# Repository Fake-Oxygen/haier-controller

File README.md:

# Haier Heat Pump Controller

Custom controller and monitoring interface for Haier heat pumps using the **YR-E27 remote-control interface / Modbus RTU**.

The project combines an embedded controller, custom hardware, firmware, and host-side tools for communicating with and monitoring the heat pump.

## Overview

The controller interfaces directly with the heat pump's communication bus and provides access to operational data and control parameters that are otherwise handled by the original control system.

The system is built around an **ESP32-C6** running **Zephyr RTOS**. The controller communicates with the heat pump over UART/Modbus RTU and exposes selected telemetry and control functionality through Wi-Fi and MQTT.

The repository also contains hardware and mechanical design files, as well as software utilities used for protocol investigation, testing, and monitoring.

## System Architecture

```text
                    ┌─────────────────────┐
                    │    Haier Heat Pump  │
                    │                     │
                    │  YR-E27 / Modbus RTU│
                    └──────────┬──────────┘
                               │
                         UART / RS-485
                               │
                    ┌──────────▼──────────┐
                    │   ESP32-C6          │
                    │                     │
                    │   Zephyr RTOS       │
                    │   Modbus client     │
                    │   Heat pump driver  │
                    │   Control logic     │
                    └───────┬───────┬─────┘
                            │       │
                          Wi-Fi    GPIO
                            │       │
                     ┌──────▼───┐   ├── Relay outputs
                     │   MQTT   │   └── Status / sensors
                     └──────────┘
```

The exact hardware interfaces and signal routing are documented in the hardware design files.

## Heat Pump Communication

The main purpose of the project is direct communication with the Haier heat pump.

Communication uses **Modbus RTU over UART**. The firmware implements the required register access and translates the heat pump's register data into higher-level operating parameters.

The implementation currently provides access to parameters including:

* CH temperature
* DHW temperature
* CH target temperature
* DHW target temperature
* Operating mode
* Valve state
* Tank status
* Heater operating state
* Other system status registers

The firmware can also write supported registers to change selected operating parameters.

The register definitions and protocol implementation are located in the firmware sources.

## Hardware

The controller is based on an **ESP32-C6**.

The hardware provides interfaces for:

* Heat pump communication
* Wi-Fi
* Temperature measurement
* Relay/control outputs
* Status indication

The complete hardware design is located in [`hw/`](./hw).

Refer to the schematics and PCB files there for the actual electrical implementation.

## Mechanical Design

Mechanical parts and enclosure designs are located in [`hwm/`](./hwm).

The enclosure is designed around the controller hardware and its intended installation environment.

Available CAD/manufacturing files should be treated as the authoritative source for dimensions and mechanical details.

## Firmware

The embedded firmware is located in [`fw/`](./fw).

It is written in **C** and uses **Zephyr RTOS**.

The firmware is responsible for:

* Modbus communication with the heat pump
* Register decoding
* Heat pump state/control handling
* Wi-Fi connectivity
* MQTT communication
* Telemetry publishing
* Local I/O such as relays and sensors

The main application and hardware-specific code are organized within the firmware tree.

## MQTT

The controller publishes heat pump telemetry over MQTT, allowing the data to be consumed by external systems such as home-automation or monitoring software.

Telemetry is encoded using **CBOR** before being published.

The MQTT interface is implemented in the firmware and is intended to decouple the heat pump interface from higher-level monitoring and automation systems.

## Host-Side Tools

The [`sw/`](./sw) directory contains software used during development and operation of the system.

These tools are separate from the ESP32 firmware and are useful for tasks such as:

* Monitoring communication
* Testing the heat pump interface
* Experimenting with the protocol
* Simulating heat pump behavior

In particular, `sniffer.py` and `mock_heatpump.py` are used for working with the communication protocol without necessarily relying on the complete embedded system.

## Building the Firmware

The firmware uses the Zephyr build system and `west`.

Initialize the project:

```bash
./init.sh
```

Build for the target board:

```bash
west build -p auto -b esp32c6_devkitc_hpcore
```

Flash the resulting firmware:

```bash
west flash
```

The required Zephyr SDK and Python dependencies must be installed before building.

## Repository Structure

```text
.
├── fw/                  # ESP32-C6 firmware
│   ├── src/             # Application code
│   ├── drivers/         # Hardware / heat pump drivers
│   └── boards/          # Board-specific configuration
│
├── hw/                  # Electronics design
│   ├── ...              # Schematics / PCB files
│   └── ...
│
├── hwm/                 # Mechanical design
│   ├── ...              # CAD / STL files
│   └── ...
│
├── sw/                  # Host-side tools
│   ├── sniffer.py       # Protocol analysis tool
│   ├── mock_heatpump.py # Heat pump simulator
│   └── ...
│
└── README.md
```

## Development Status

This repository contains an actively developed controller and reverse-engineering effort for interfacing with the Haier heat pump communication system.

The firmware, hardware, and host-side tooling are maintained together because development of the controller depends on understanding and testing the heat pump's communication protocol.

For the current implementation status, refer to the firmware and software sources rather than assuming that every documented interface is production-ready.

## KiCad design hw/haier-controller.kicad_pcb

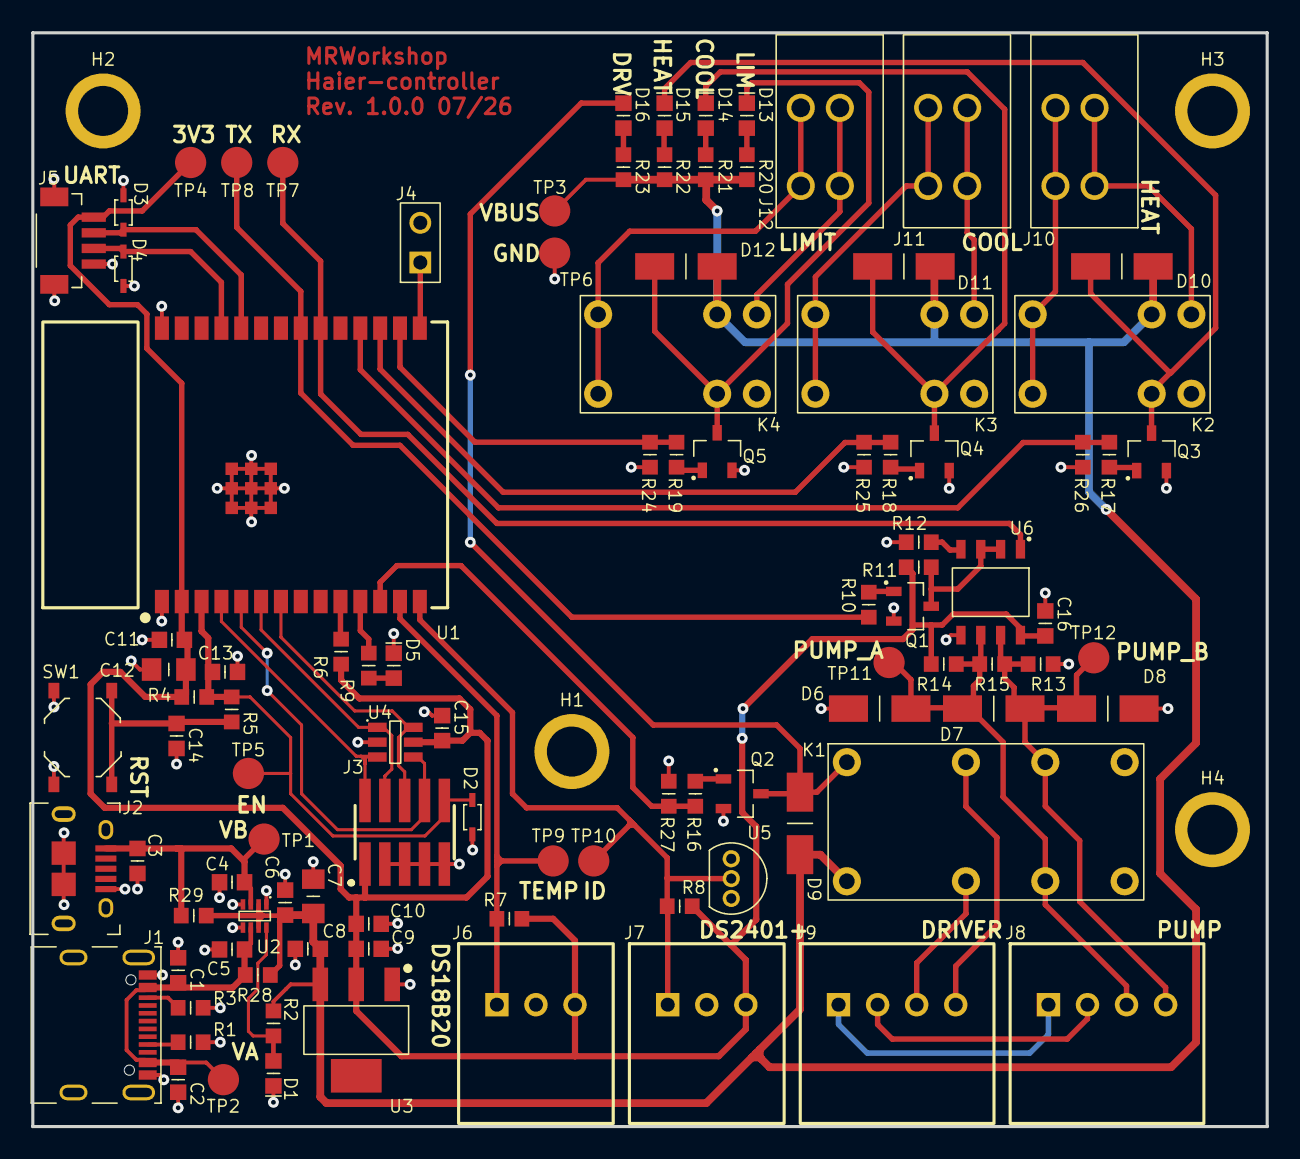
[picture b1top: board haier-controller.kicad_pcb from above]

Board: 2 copper layers, 79.0 x 70.0 mm, 105 parts (0 on the bottom side), 55 nets.

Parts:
C1, C2, C3, C13: 1u; C_0603
C4, C5, C6, C8, C9, C11, C14, C15, C16: 100n; C_0603
C7: 10u; C_0805
C10: 10u; C_0603
C12: 22uF; C_0805
D1, D5, D13, D14, D15, D16: Green; LED_0603
D2, D3, D4: STS321033B100; SOD-323
D6, D7, D8: SMAJ12CA-13-F; SMA
D9, D10, D11, D12: M7; SMA
H1, H2, H3, H4: M3; M3-Hole
J1: USB4105-GF-A
J2: 10118194-0001LF
J3: FTSH-105-01-L-DV-K
J4: Goldpin; Goldpin 2.54mm 1x2 Vertical
J5: BM04B; BM04B-SRSS-TB (LF)(SN)
J6, J7: S3B-XH-A-1; S3B-XH-A-1 (LF)(SN)
J8, J9: S4B-XH-A-1; S4B-XH-A-1 (LF)(SN)
J10, J11, J12: DG240W; DG240W-2.54-02P-15-00A(H)
K1: HFD27-005-S
K2, K3, K4: HFD23/005-1ZS; HFD23-005-1ZS
Q1, Q2, Q3, Q4, Q5: MMBT3904; SOT-23
R1, R3: 5k1; R_0603
R2, R9, R16, R17, R18, R19, R20, R21, R22, R23: 1k; R_0603
R4, R6, R24, R25, R26, R27: 10k; R_0603
R5, R12, R28, R29: 0R; R_0603
R7, R8, R10, R11, R13, R14: 4k7; R_0603
R15: 120R; R_0603
SW1: PTS526SM15SMTR2_LFS
TP1, TP2, TP3, TP4, TP5, TP6, TP7, TP8, TP9, TP10, TP11, TP12: TestPoint-2mm
U1: ESP32-C6; ESP32-C6-WROOM-1
U2: LM66200DRLR; SOT8
U3: LD1117S33CTR; SOT-223
U4: USBLC6-4SC6; SOT23-6L
U5: DS2401+; TO-92
U6: MAX3485EESA+T; SO8

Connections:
+3.3V: C9.2, C10.2, C11.2, C12.2, C15.2, C16.1, J3.1 (VREF), J5.1, J6.3, J7.3, R4.1, R6.2, R7.1, R8.1, R11.1, R14.1, TP4.1, U1.2 (3V3), U3.2 (VOUT), U4.5 (VBUS), U6.8 (VCC)
/1W_ID: J7.1, R8.2, TP10.1, U1.14 (IO13), U5.2 (DATA)
/COOL_SW: R18.2, R25.2, U1.17 (IO19)
/DRV_A: J9.3, K1.7 (NC2)
/DRV_B: J9.4, K1.2 (NC1)
/DS18B20: J6.1, R7.2, TP9.1, U1.13 (IO12)
/ESP_EN: C13.2, D2.2, J3.10 (RST), R4.2, R5.1, TP5.1, U1.3 (EN)
/ESP_TCK: J3.4 (TCK/SWDCLK), U1.6 (IO6), U4.1 (I/O1)
/ESP_TDI: J3.8 (TDI), U1.5 (IO5), U4.4 (I/O3)
/ESP_TDO: J3.6 (TDO/SWO), U1.7 (IO7), U4.6 (I/O4)
/ESP_TMS: J3.2 (TMS/SWDIO), U1.4 (IO4), U4.3 (I/O2)
/HEAT_SW: R17.2, R26.2, U1.18 (IO20)
/LIM_SW: R19.2, R24.2, U1.16 (IO18)
/PUMP_A: D6.1, D7.2, J8.3, K1.6 (COM2), R14.2, R15.1, TP11.1, U6.6 (A)
/PUMP_B: D7.1, D8.2, J8.4, K1.3 (COM1), R13.1, R15.2, TP12.1, U6.7 (B)
/PUMP_RX: TP7.1, U1.20 (IO22), U6.1 (RO)
/PUMP_TX: R10.1, TP8.1, U1.21 (IO23)
/RS_SWITCH: R16.2, R27.2, U1.12 (IO11)
GND: C1.1, C2.1, C3.1, C4.1, C5.1, C6.1, C7.1, C8.1, C9.1, C10.1, C11.1, C12.1, C13.1, C14.1, C15.1, C16.2, D1.1, D2.1, D3.1, D4.1, D5.1, D6.2, D8.1, H1.1, H2.1, H3.1, H4.1, J1.A1 (GND), J1.A12 (GND), J1.SH (Shield), J2.5 (GND), J2.SH, J3.3 (GND), J3.5 (GND), J3.7 (VDD), J3.9 (GND), J4.2, J5.4, J5.SH, J6.2, J7.2, Q1.3 (E), Q2.3 (E), Q3.3 (E), Q4.3 (E), Q5.3 (E), R1.1, R3.1, R12.2, R13.2, R24.1, R25.1, R26.1, R27.1, SW1.2, TP6.1, U1.1 (GND), U1.28 (GND), U1.29 (EPAD), U2.1 (GND), U2.4 (~ON), U2.5 (GND), U3.1 (GND), U4.2 (GND), U5.1 (GND), U6.5 (GND)
unnamed: C14.2, R5.2, SW1.1
unnamed: D5.2, R9.1
unnamed: D13.2, R20.2
unnamed: D14.2, R21.2
unnamed: D15.2, R22.2
unnamed: D16.2, R23.2
unnamed: J1.A5 (CC1), R3.2
unnamed: J1.B5 (CC2), R1.2
unnamed: J8.1, J9.1
unnamed: J8.2, J9.2
unnamed: J10.2, K2.3 (COM1), K2.4 (COM1)
unnamed: J11.2, K3.3 (COM1), K3.4 (COM1)
unnamed: J12.2, K4.3 (COM1), K4.4 (COM1)
unnamed: D9.2, D16.1, K1.1 (VCC), Q2.2 (C)
unnamed: J10.1, K2.6 (NO1)
unnamed: D10.2, D15.1, K2.2 (VCC), Q3.2 (C)
unnamed: J11.1, K3.6 (NO1)
unnamed: D11.2, D14.1, K3.2 (VCC), Q4.2 (C)
unnamed: J12.1, K4.6 (NO1)
unnamed: D12.2, D13.1, K4.2 (VCC), Q5.2 (C)
unnamed: Q1.1 (B), R10.2
unnamed: Q1.2 (C), R11.2, U6.2 (~RE), U6.3 (DE)
unnamed: Q2.1 (B), R16.1
unnamed: Q3.1 (B), R17.1
unnamed: Q4.1 (B), R18.1
unnamed: Q5.1 (B), R19.1
unnamed: R6.1, U1.10 (IO8)
unnamed: J4.1, U1.15 (IO9)
unnamed: R9.2, U1.11 (IO10)
unnamed: D3.2, J5.2, U1.24 (RXD0)
unnamed: D4.2, J5.3, U1.25 (TXD0)
unnamed: D1.2, R2.2, U2.8 (ST)
unnamed: R12.1, U6.4 (DI)
VBUS: C6.2, C7.2, C8.2, D9.1, D10.1, D11.1, D12.1, K1.8 (GND), K2.5 (GND), K3.5 (GND), K4.5 (GND), R2.1, R20.1, R21.1, R22.1, R23.1, R28.1, R29.1, TP3.1, U2.2 (VOUT), U2.7 (VOUT), U3.3 (VIN)
VBUS_A: C1.2, C2.2, C5.2, J1.A4 (VBUS), J1.A9 (VBUS), R28.2, TP2.1, U2.6 (VIN2)
VBUS_B: C3.2, C4.2, J2.1 (VCC), R29.2, TP1.1, U2.3 (VIN1)
